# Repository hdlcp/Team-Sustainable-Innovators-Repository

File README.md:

# Team-Sustainable-Innovators-Repository
This repository contains the full technical implementation of the HydroNex project, developed by the Sustainable Innovators team for the GAIAthon 2025 competition.
HydroNex is a solar-powered floating IoT device designed to monitor coastal water quality in real time.

The repository is structured into three main folders:

IoT_Device/ – Contains all IoT-related files including:

Hardware schematics and wiring diagrams

PCB design files

3D casing model

Firmware source code (ESP8266)

Calibration notes and sensor documentation

API_Backend/ – Flask-based REST API to handle data transmission, storage, and access.

Flask project source code

API routes and logic

Swagger documentation

Dashboard_Frontend/ – React.js frontend dashboard for real-time data visualization and user interaction.

User interface source code

Alert and recommendation system

HydroBot chatbot integration

Newsletter subscription system

This repository reflects the end-to-end development of the HydroNex solution, including hardware, software, and deployment.

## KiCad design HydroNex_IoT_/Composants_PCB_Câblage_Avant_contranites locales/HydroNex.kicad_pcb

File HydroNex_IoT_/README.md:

# HydroNex - Module Électronique de Surveillance

Module électronique basé sur ESP32 pour la surveillance de la qualité des eaux côtières avec alimentation solaire.

## 📸 Aperçu du module

| Schéma électronique | Layout PCB | Rendu 3D |
|:---:|:---:|:---:|
|  |  |  |
| *Schéma électronique complet* | *Layout PCB optimisé* | *Rendu 3D du module* |

## 📋 Vue d'ensemble

Module électronique pour la mesure en temps réel des paramètres de qualité d'eau : pH, turbidité, température, salinité et niveau de batterie. Les données sont transmises via Wi-Fi.

## 🔧 Composants principaux

### Microcontrôleur
- **ESP32** (ESP32_DEVKIT) - Microcontrôleur WiFi/Bluetooth dual-core

### Capteurs de qualité d'eau
- **SAL** (TBLOCK-J2) - Capteur de salinité
- **TURB** - Capteur de turbidité  
- **PH** (25630301RP2) - Capteur de pH
- **THER** (TBLOCK-J3) - Capteur de température

### Alimentation
- **PV** (TBLOCK-J2) - Entrée panneau solaire
- **BAT** (TBLOCK-J2) - Connexion batterie
- **U1** (7805) - Régulateur de tension 5V
- **INT** (TBLOCK-J2) - Interface de contrôle

### Interfaces
- **IN** (TBLOCK-J2) - Entrée générale
- **OUT** (TBLOCK-J2) - Sortie générale

### Composants passifs
- **R1** (4k7) - Résistance pull-up
- **R2** (10k) - Résistance de polarisation  
- **R3** (10k) - Résistance de polarisation
- **R4** (4k7) - Résistance pull-up

## 📐 Caractéristiques du PCB

- **Format** : Module compact étanche
- **Couches** : PCB multicouches optimisé
- **Connecteurs** : Blocs terminaux à vis pour connexions externes
- **Alimentation** : Support panneau solaire et batterie avec régulation 5V/3.3V
- **Protection** : Design résistant aux conditions marines

## 🔌 Brochage et connexions

### ESP32 (ESP32_DEVKIT)
- **GPIO** configurables pour les capteurs
- **ADC** pour lecture des niveaux de batterie
- **VIN/GND** pour l'alimentation
- **WiFi** pour transmission des données

### Blocs terminaux
- **PV** : Connexion panneau solaire (entrée alimentation)
- **BAT** : Connexion batterie (stockage énergie)
- **SAL** : Connexion capteur de salinité
- **TURB** : Connexion capteur de turbidité  
- **PH** : Connexion capteur de pH
- **THER** : Connexion capteur de température
- **INT** : Interface de contrôle système
- **IN/OUT** : Entrées/sorties auxiliaires

## ⚡ Alimentation et gestion de l'énergie

- **Entrée principale** : Panneau solaire via connecteur PV
- **Stockage** : Batterie rechargeable via connecteur BAT
- **Régulation** : 7805 pour 5V stable, ESP32 régule en 3.3V
- **Monitoring** : Surveillance du niveau de batterie transmise avec les données
- **Optimisation** : Mode veille entre les mesures pour économiser l'énergie

## 📊 Données transmises

Le module transmet via Wi-Fi les paramètres suivants :
- **pH** - Acidité/basicité de l'eau
- **Turbidité** - Clarté de l'eau
- **Température** - Température de l'eau
- **Salinité** - Concentration en sel
- **Niveau batterie** - État de charge pour maintenance

## 🚀 Configuration

### Prérequis
- Arduino IDE ou PlatformIO
- Bibliothèques ESP32
- Drivers USB-UART pour programmation

### Installation
1. Connecter le module via USB
2. Configurer les paramètres capteurs
3. Définir les credentials Wi-Fi
4. Compiler et téléverser le firmware
5. Tester les connexions capteurs

## 🔗 Connectivité

- **WiFi** : Transmission automatique des données
- **UART** : Programmation et debug via USB
- **GPIO** : Interfaces configurables pour extensions

---

### Stockage
- **Local** : Mémoire flash ESP32 (backup)
- **Cloud** : Transmission vers serveur/base de données
- **Fréquence** : Configurable (15min - 1h)

## 🛠️ Installation et Déploiement

### Préparation
1. Vérifier l'étanchéité de tous les joints
2. Charger complètement la batterie
3. Tester la connectivité WiFi
4. Calibrer les capteurs si nécessaire

### Déploiement
1. Placer délicatement sur l'eau
2. Vérifier la stabilité et l'orientation
3. Confirmer la transmission des données
4. Noter la position GPS (si applicable)

### Maintenance
- **Nettoyage** : Toutes les 2 semaines
- **Calibration** : Mensuelle
- **Batterie** : Vérification hebdomadaire
- **Joints** : Inspection trimestrielle

## 🤝 Contribution

Les contributions sont les bienvenues ! N'hésitez pas à :
- Signaler des bugs
- Proposer des améliorations
- Ajouter de nouveaux capteurs
- Optimiser le code

**Note** : Vérifiez l'étanchéité de tous les connecteurs avant déploiement en milieu marin. Respectez les spécifications des capteurs pour éviter tout dommage par l'eau salée.

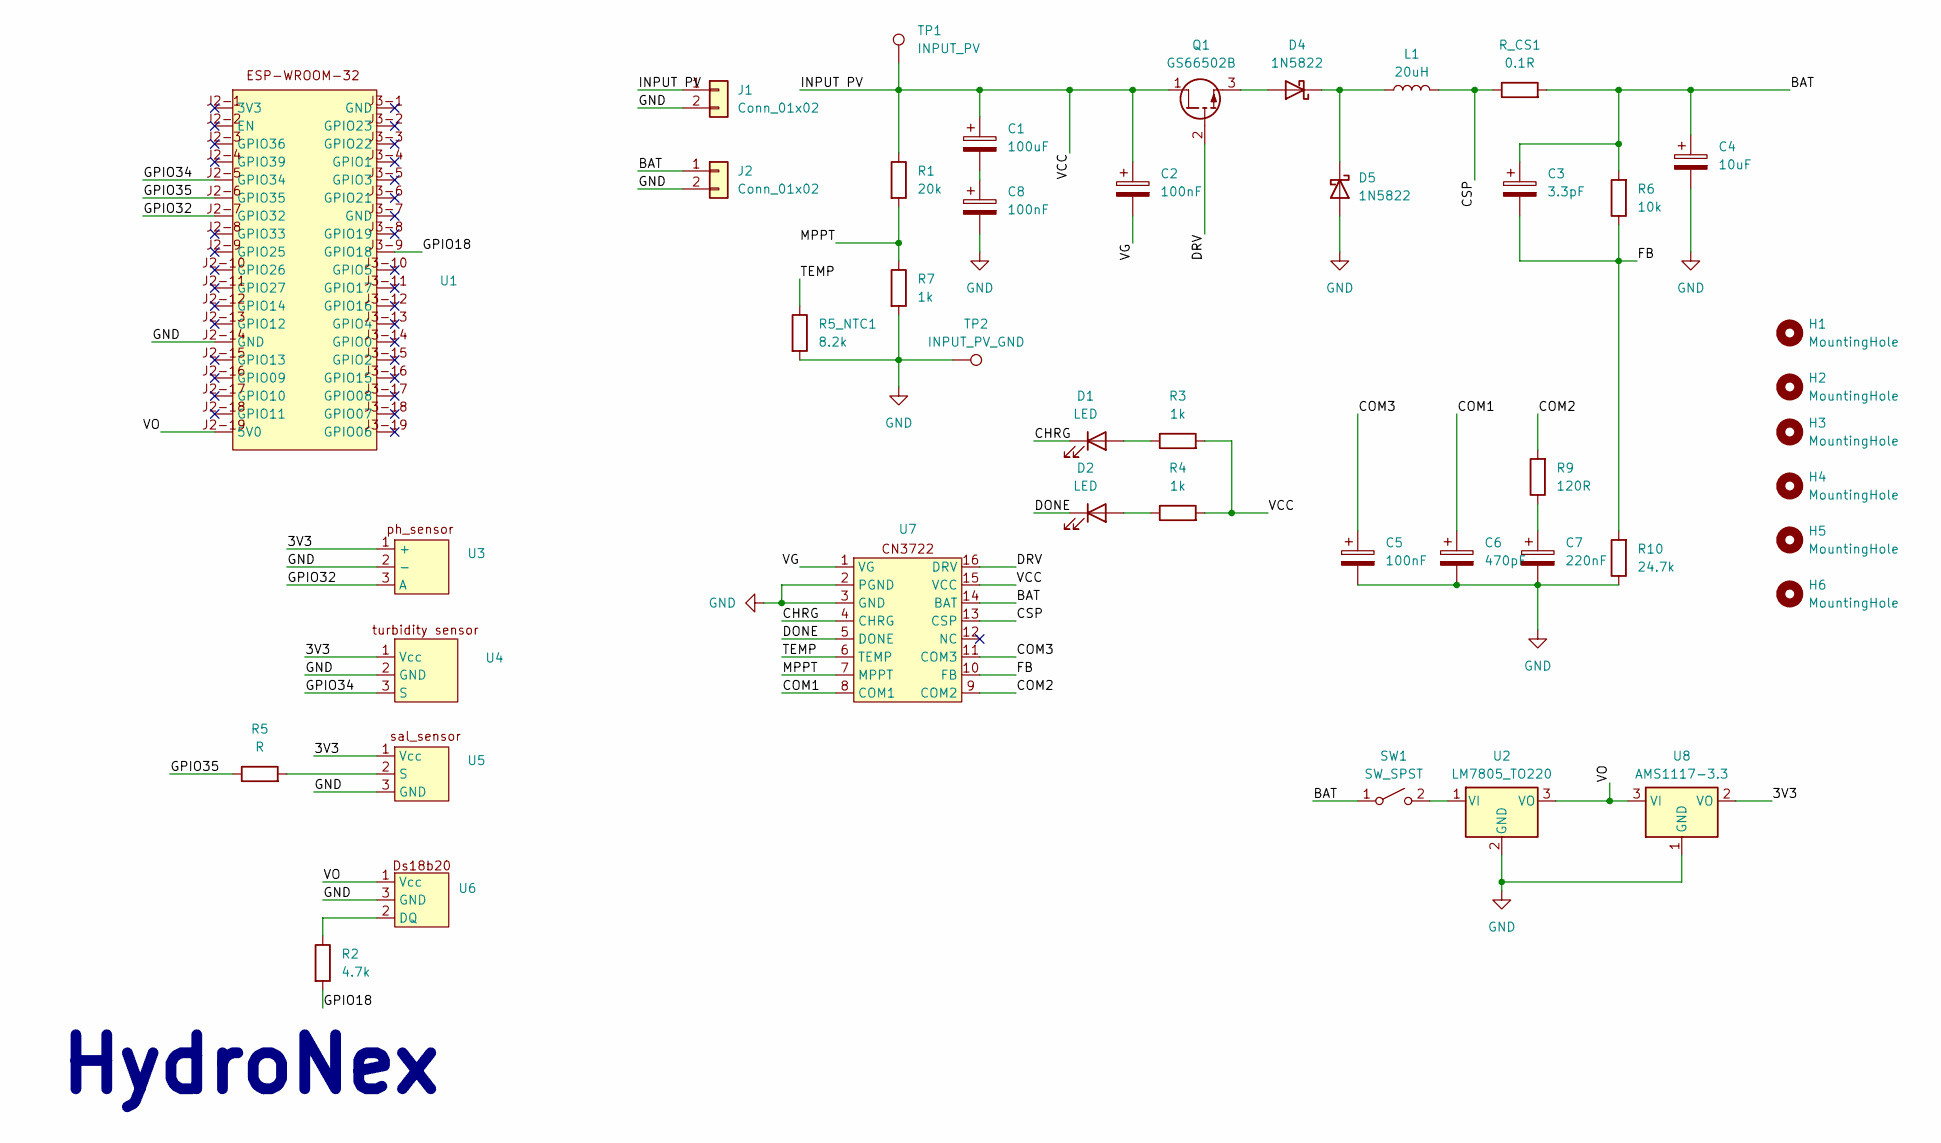
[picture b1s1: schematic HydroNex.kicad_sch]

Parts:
C1: 100uF; CP_Radial_D5.0mm_P2.00mm
C2, C5, C8: 100nF; C_Disc_D3.4mm_W2.1mm_P2.50mm
C3: 3.3pF; C_Disc_D6.0mm_W4.4mm_P5.00mm
C4: 10uF; CP_Radial_D5.0mm_P2.00mm
C6: 470pF; C_Disc_D6.0mm_W4.4mm_P5.00mm
C7: 220nF; C_Disc_D5.1mm_W3.2mm_P5.00mm
D1, D2: LED; LED_D3.0mm
D4, D5: 1N5822; D_DO-34_SOD68_P7.62mm_Horizontal
H1, H2, H3, H4, H5, H6: MountingHole; MountingHole_2.5mm
J1, J2: Conn_01x02; TerminalBlock_MaiXu_MX126-5.0-02P_1x02_P5.00mm
L1: 20uH; L_Radial_D7.8mm_P5.00mm_Fastron_07HCP
Q1: GS66502B; TO254P1016X419X2286-3
R1: 20k; R_Axial_DIN0207_L6.3mm_D2.5mm_P7.62mm_Horizontal
R2: 4.7k; R_Axial_DIN0207_L6.3mm_D2.5mm_P7.62mm_Horizontal
R3, R4, R7: 1k; R_Axial_DIN0207_L6.3mm_D2.5mm_P7.62mm_Horizontal
R5: R; R_Axial_DIN0309_L9.0mm_D3.2mm_P12.70mm_Horizontal
R5_NTC1: 8.2k; R_Axial_DIN0207_L6.3mm_D2.5mm_P7.62mm_Horizontal
R6: 10k; R_Axial_DIN0207_L6.3mm_D2.5mm_P7.62mm_Horizontal
R9: 120R; R_Axial_DIN0207_L6.3mm_D2.5mm_P7.62mm_Horizontal
R10: 24.7k; R_Axial_DIN0207_L6.3mm_D2.5mm_P7.62mm_Horizontal
R_CS1: 0.1R; R_Axial_DIN0207_L6.3mm_D2.5mm_P7.62mm_Horizontal
SW1: SW_SPST; PinHeader_1x02_P2.00mm_Vertical
TP1: INPUT_PV; TestPoint_Pad_D1.5mm
TP2: INPUT_PV_GND; TestPoint_Pad_D1.5mm
U1: MODULE_ESP32-DEVKITC-32D
U2: LM7805_TO220; TO-220-3_Vertical
U3, U4, U5, U6: TerminalBlock_MaiXu_MX126-5.0-03P_1x03_P5.00mm
U7: SOIC16_CN3722_CNA
U8: AMS1117-3.3; SOT-223-3_TabPin2

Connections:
/3V3: U3.1 (+), U4.1 (Vcc), U5.1 (Vcc), U8.2 (VO)
/BAT: C3.1, C4.1, J2.1, R6.2, R_CS1.2, SW1.1 (A), U7.14 (BAT)
/CHRG: D1.1 (K), U7.4 (CHRG)
/COM1: C6.1, U7.8 (COM1)
/COM2: R9.2, U7.9 (COM2)
/COM3: C5.1, U7.11 (COM3)
/CSP: L1.2, R_CS1.1, U7.13 (CSP)
/DONE: D2.1 (K), U7.5 (DONE)
/DRV: Q1.2 (G), U7.16 (DRV)
/FB: C3.2, R6.1, R10.2, U7.10 (FB)
/GPIO18: R2.2, U1.J3-9 (GPIO18)
/GPIO32: U1.J2-7 (GPIO32), U3.3 (A)
/GPIO34: U1.J2-5 (GPIO34), U4.3 (S)
/GPIO35: R5.1, U1.J2-6 (GPIO35)
/INPUT PV: C1.1, C2.1, J1.1, Q1.1 (D), R1.1, R3.2, R4.2, TP1.1, U7.15 (VCC)
/MPPT: R1.2, R7.1, U7.7 (MPPT)
/TEMP: R5_NTC1.1, U7.6 (TEMP)
/VG: C2.2, U7.1 (VG)
/VO: U1.J2-19 (5V0), U2.3 (VO), U6.1 (Vcc), U8.3 (VI)
GND: C4.2, C5.2, C6.2, C7.2, C8.2, D5.2 (A), J1.2, J2.2, R5_NTC1.2, R7.2, R10.1, TP2.1, U1.J2-14 (GND), U2.2 (GND), U3.2 (-), U4.2 (GND), U5.3 (GND), U6.3 (GND), U7.2 (PGND), U7.3 (GND), U8.1 (GND)
unnamed: C1.2, C8.1
unnamed: C7.1, R9.1
unnamed: D1.2 (A), R3.1
unnamed: D2.2 (A), R4.1
unnamed: D4.2 (A), Q1.3 (S)
unnamed: D4.1 (K), D5.1 (K), L1.1
unnamed: SW1.2 (B), U2.1 (VI)
unnamed: R5.2, U5.2 (S)
unnamed: R2.1, U6.2 (DQ)

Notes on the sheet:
HydroNex

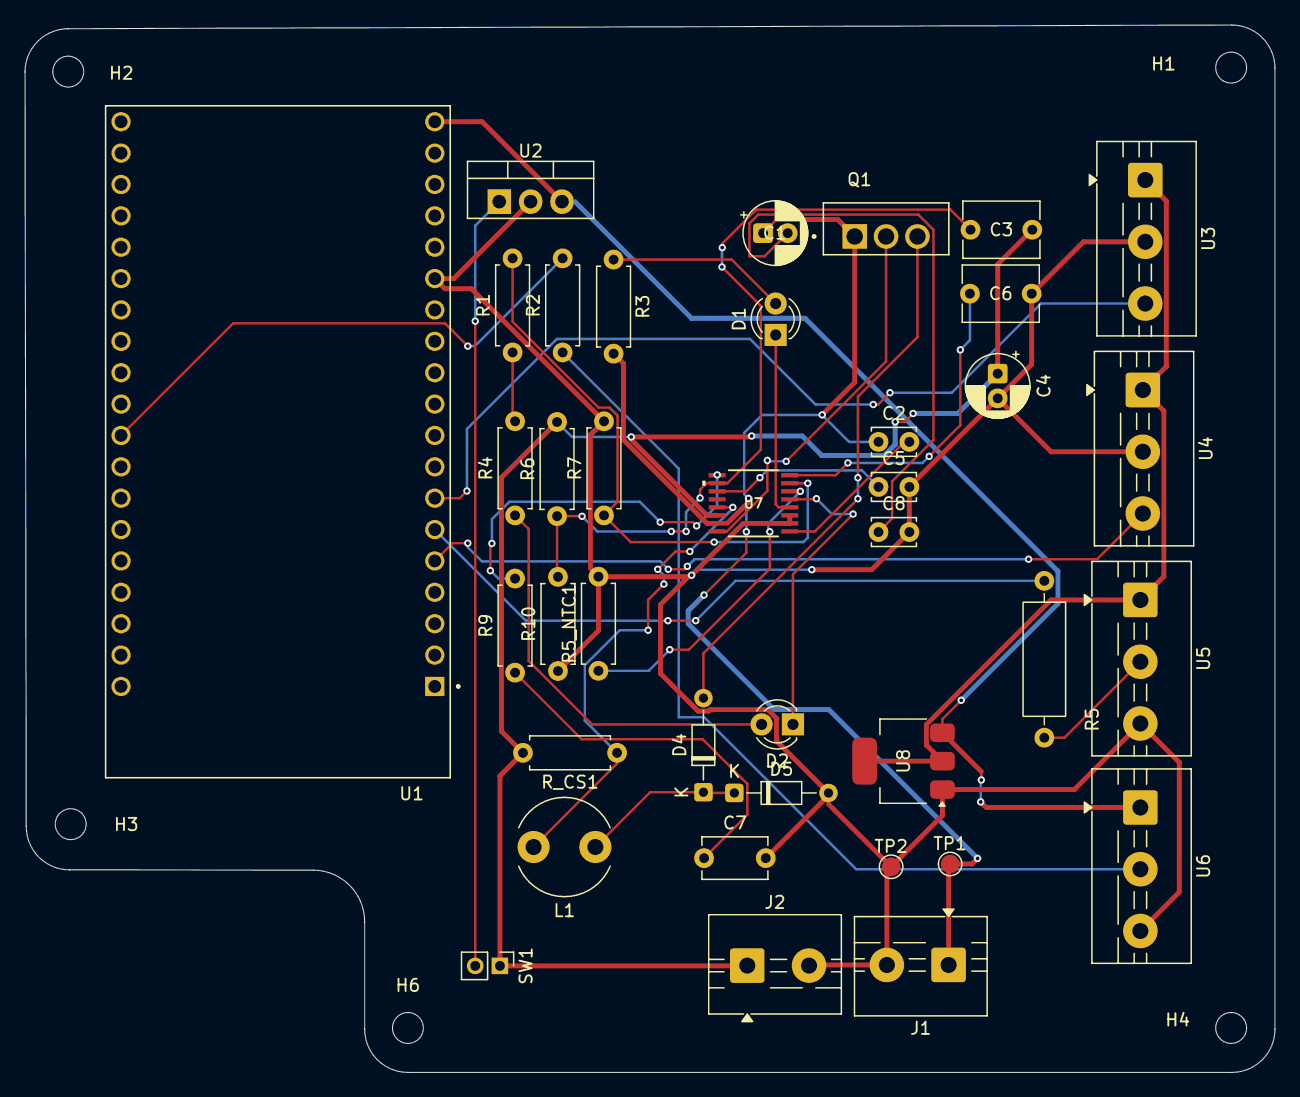
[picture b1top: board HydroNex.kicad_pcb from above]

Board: 2 copper layers, 101.2 x 84.8 mm, 43 parts (0 on the bottom side), 29 nets.

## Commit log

2025-06-27 Initial commit - HydroNex project
2025-06-29 ajout de Readme
